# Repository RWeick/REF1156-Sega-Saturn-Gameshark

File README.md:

# REF1156-Sega-Saturn-Gameshark
Everything necessary to produce a Gameshark for the Sega Saturn. The original PCB had a 100 nF capacitor bodged on in addition to the three SMD capacitors. I have added a 4th SMD capacitor to resolve that.

PCB Thickness: 1.6 mm

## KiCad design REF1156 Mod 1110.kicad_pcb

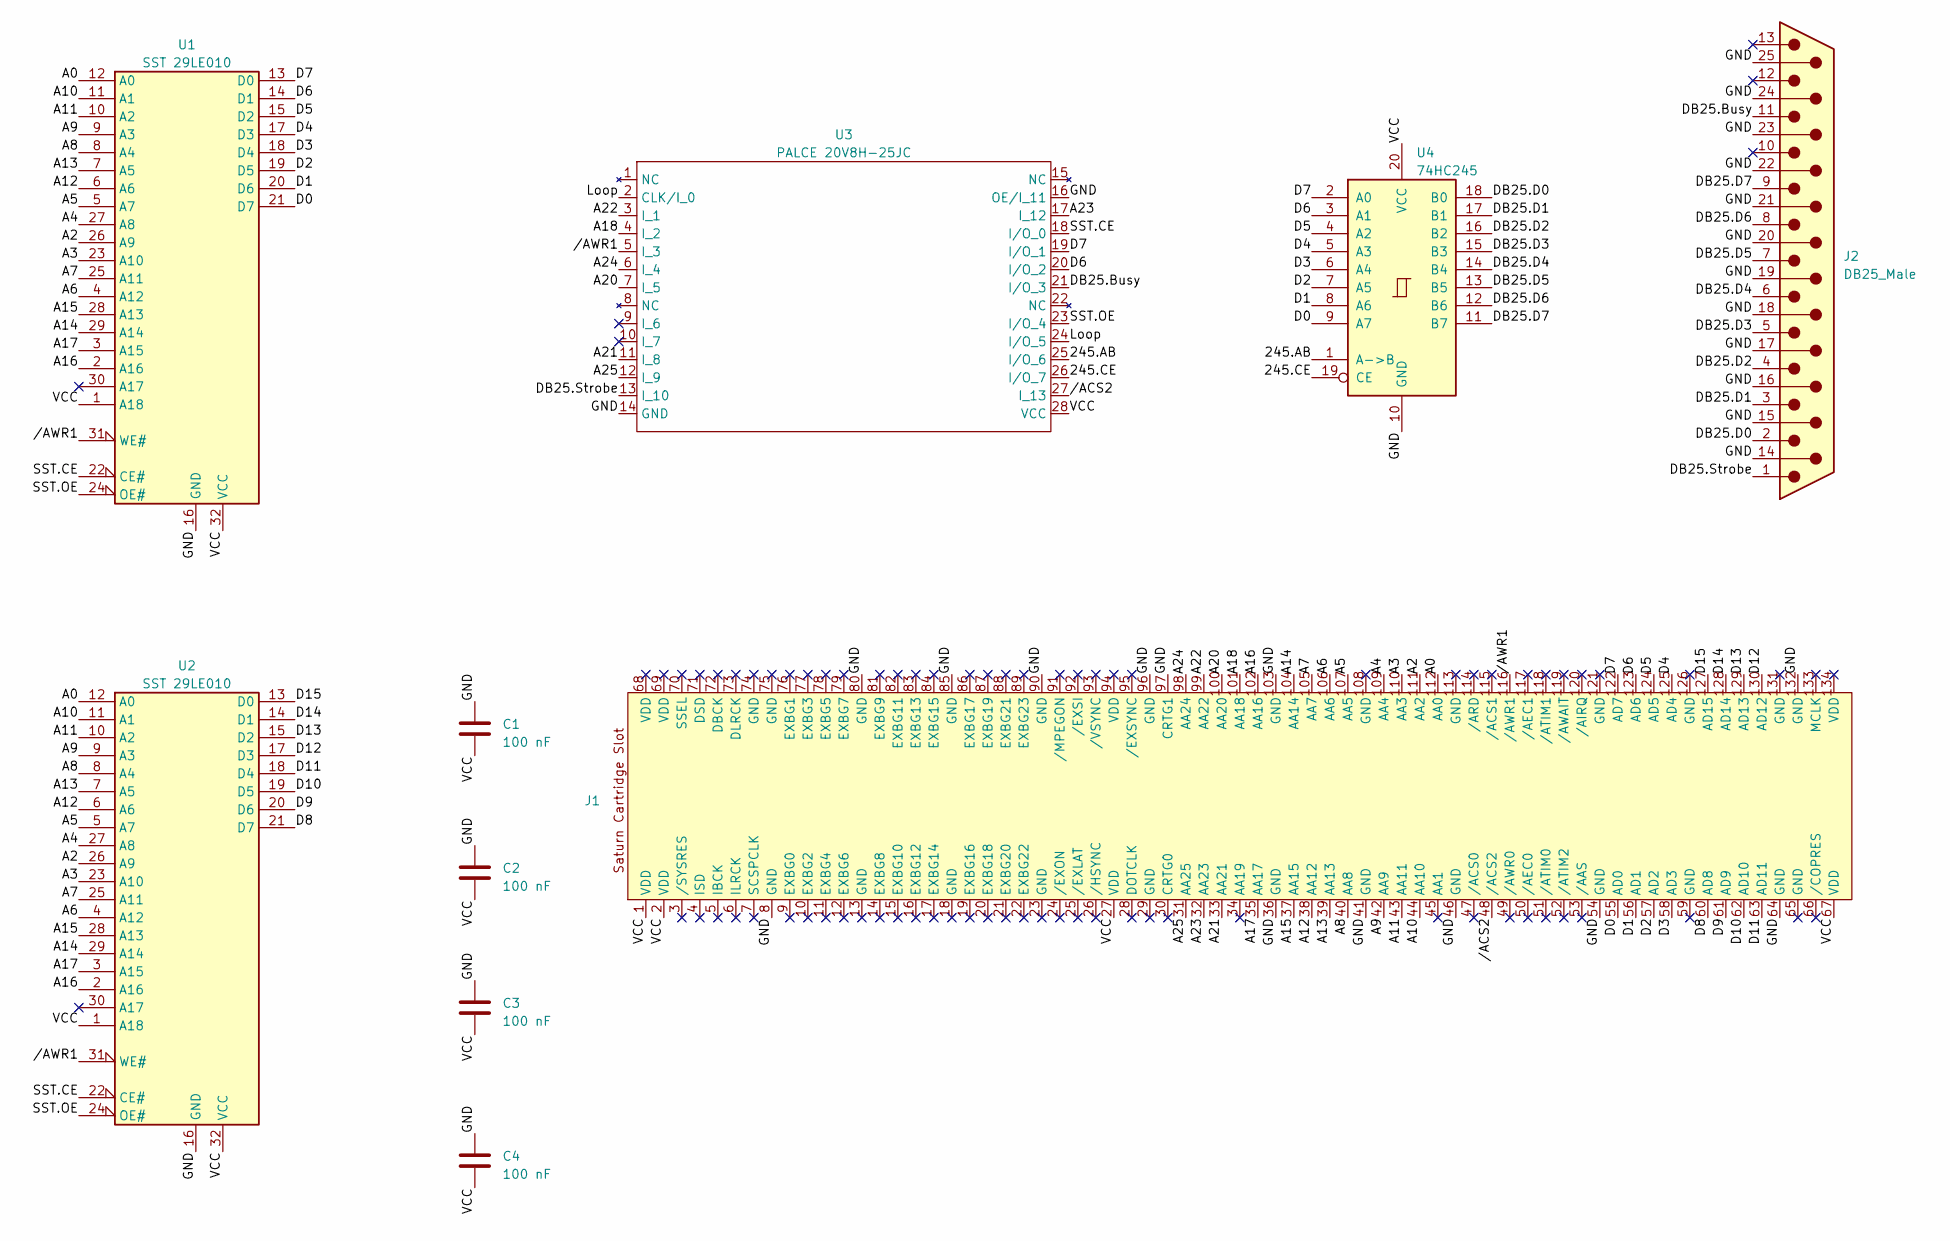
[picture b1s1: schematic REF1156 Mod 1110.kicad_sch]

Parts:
C1, C2, C3, C4: 100 nF; C_1206_3216Metric_Pad1.33x1.80mm_HandSolder
J1: Cartridge Connector
J2: DB25_Male; DSUB-25_Male_EdgeMount_P2.77mm
U1, U2: SST 29LE010; PLCC-32_11.4x14.0mm_P1.27mm
U3: PALCE 20V8H-25JC; PLCC-28
U4: 74HC245

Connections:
/245.AB: U3.25 (I/O_6), U4.1 (A->B)
/245.CE: U3.26 (I/O_7), U4.19 (CE)
/A0: J1.112 (AA0), U1.12 (A0), U2.12 (A0)
/A2: J1.111 (AA2), U1.26 (A9), U2.26 (A9)
/A3: J1.110 (AA3), U1.23 (A10), U2.23 (A10)
/A4: J1.109 (AA4), U1.27 (A8), U2.27 (A8)
/A5: J1.107 (AA5), U1.5 (A7), U2.5 (A7)
/A6: J1.106 (AA6), U1.4 (A12), U2.4 (A12)
/A7: J1.105 (AA7), U1.25 (A11), U2.25 (A11)
/A8: J1.40 (AA8), U1.8 (A4), U2.8 (A4)
/A9: J1.42 (AA9), U1.9 (A3), U2.9 (A3)
/A10: J1.44 (AA10), U1.11 (A1), U2.11 (A1)
/A11: J1.43 (AA11), U1.10 (A2), U2.10 (A2)
/A12: J1.38 (AA12), U1.6 (A6), U2.6 (A6)
/A13: J1.39 (AA13), U1.7 (A5), U2.7 (A5)
/A14: J1.104 (AA14), U1.29 (A14), U2.29 (A14)
/A15: J1.37 (AA15), U1.28 (A13), U2.28 (A13)
/A16: J1.102 (AA16), U1.2 (A16), U2.2 (A16)
/A17: J1.35 (AA17), U1.3 (A15), U2.3 (A15)
/A18: J1.101 (AA18), U3.4 (I_2)
/A20: J1.100 (AA20), U3.7 (I_5)
/A21: J1.33 (AA21), U3.11 (I_8)
/A22: J1.99 (AA22), U3.3 (I_1)
/A23: J1.32 (AA23), U3.17 (I_12)
/A24: J1.98 (AA24), U3.6 (I_4)
/A25: J1.31 (AA25), U3.12 (I_9)
/D0: J1.55 (AD0), U1.21 (D7), U4.9 (A7)
/D1: J1.56 (AD1), U1.20 (D6), U4.8 (A6)
/D2: J1.57 (AD2), U1.19 (D5), U4.7 (A5)
/D3: J1.58 (AD3), U1.18 (D4), U4.6 (A4)
/D4: J1.125 (AD4), U1.17 (D3), U4.5 (A3)
/D5: J1.124 (AD5), U1.15 (D2), U4.4 (A2)
/D6: J1.123 (AD6), U1.14 (D1), U3.20 (I/O_2), U4.3 (A1)
/D7: J1.122 (AD7), U1.13 (D0), U3.19 (I/O_1), U4.2 (A0)
/D8: J1.60 (AD8), U2.21 (D7)
/D9: J1.61 (AD9), U2.20 (D6)
/D10: J1.62 (AD10), U2.19 (D5)
/D11: J1.63 (AD11), U2.18 (D4)
/D12: J1.130 (AD12), U2.17 (D3)
/D13: J1.129 (AD13), U2.15 (D2)
/D14: J1.128 (AD14), U2.14 (D1)
/D15: J1.127 (AD15), U2.13 (D0)
/DB25.Busy: J2.11, U3.21 (I/O_3)
/DB25.D0: J2.2, U4.18 (B0)
/DB25.D1: J2.3, U4.17 (B1)
/DB25.D2: J2.4, U4.16 (B2)
/DB25.D3: J2.5, U4.15 (B3)
/DB25.D4: J2.6, U4.14 (B4)
/DB25.D5: J2.7, U4.13 (B5)
/DB25.D6: J2.8, U4.12 (B6)
/DB25.D7: J2.9, U4.11 (B7)
/DB25.Strobe: J2.1, U3.13 (I_10)
/GND: C1.1, C2.1, C3.1, C4.2, J1.8 (GND), J1.36 (GND), J1.41 (GND), J1.46 (GND), J1.54 (GND), J1.64 (GND), J1.80 (GND), J1.85 (GND), J1.90 (GND), J1.96 (GND), J1.97 (CRTG1), J1.103 (GND), J1.132 (GND), J2.14, J2.15, J2.16, J2.17, J2.18, J2.19, J2.20, J2.21, J2.22, J2.23, J2.24, J2.25, U1.16 (GND), U2.16 (GND), U3.14 (GND), U3.16 (OE/I_11), U4.10 (GND)
/Loop: U3.2 (CLK/I_0), U3.24 (I/O_5)
/SST.CE: U1.22 (CE#), U2.22 (CE#), U3.18 (I/O_0)
/SST.OE: U1.24 (OE#), U2.24 (OE#), U3.23 (I/O_4)
/VCC: C1.2, C2.2, C3.2, C4.1, J1.1 (VDD), J1.2 (VDD), J1.27 (VDD), J1.67 (VDD), U1.1 (A18), U1.32 (VCC), U2.1 (A18), U2.32 (VCC), U3.28 (VCC), U4.20 (VCC)
//ACS2: J1.48 (/ACS2), U3.27 (I_13)
//AWR1: J1.116 (/AWR1), U1.31 (WE#), U2.31 (WE#), U3.5 (I_3)

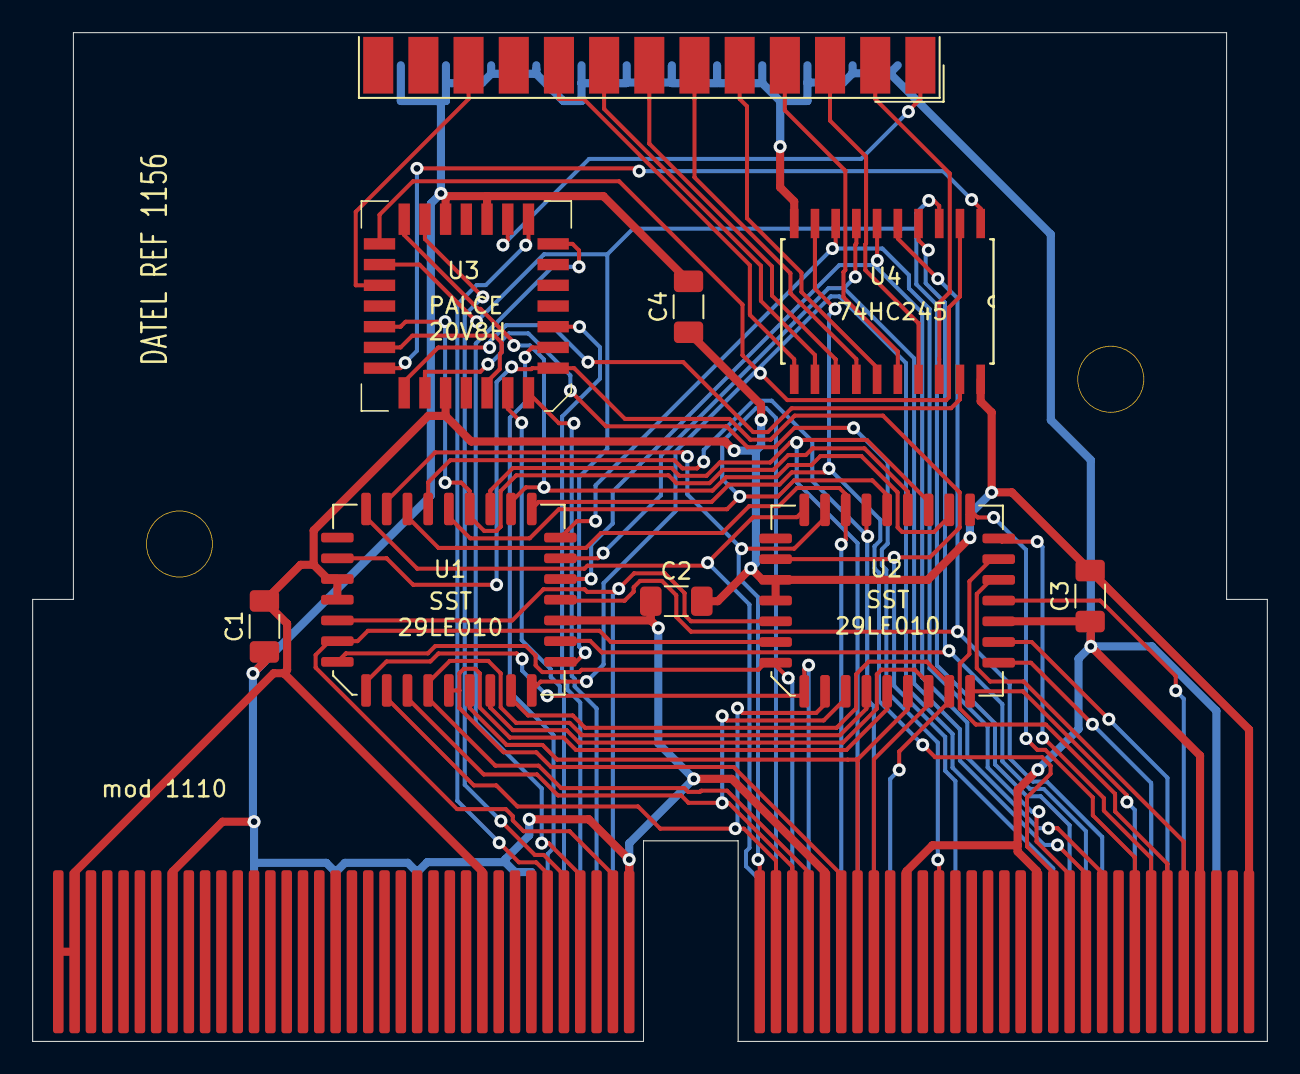
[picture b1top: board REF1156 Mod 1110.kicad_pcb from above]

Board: 2 copper layers, 75.7 x 61.8 mm, 11 parts (0 on the bottom side), 59 nets.

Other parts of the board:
Holes: Drill Holes

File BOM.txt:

2x SST 29LE010
1x PALCE 20V8H-25JC/4 PLCC 28 Package
1x 74HC245A SOIC-20 Package
3x 100 nF Capacitors 1218 package
1x Ceramic Disc Capacitor 50V 100nF 104 Marking
1x DB25 Parallel Port Adapter, Male
